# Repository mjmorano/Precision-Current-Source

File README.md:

# Overview
This is all of the design files and the code needed for my precision current source. The code for the microcontroller was made using the Arduino framework and PlatformIO so it's easy to modify and can be uploaded without neededing a programmer, just an Arduino. The serial interface features a few basic commands for setting the current and reading it back using the onboard ADC, as well as reading the internal temperature sensors. I added a lot of error checking to the firmware so it should be basically impossible to make the device do something that it shouldn't, and give the user feedback if their inputs are accepted or not. This design uses an external voltage source up to 100 volts, so it can be used with relatively high resistance loads. It is also suitable for high inductance loads, and has been verified stable into 250 mH. The KiCad folder contains all of the schematics and the .zip files with the gerbers needed to have the PCBs and the front panel manufactured. I have the front panels made as aluminum PCBs with no copper layers, which pretty much any manufacturer can do.

# Stability Measurement
Since this is meant to be used for driving gradient and shim coils for long experimental runs, temperature stability is critical. To measure the stability I rented a Keysight 3458A and logged data for a week at maximum output current and the result can be seen in the plot below. Allan deviations for this data are also shown. The current stability could be further improved by using a different voltage reference, the LTZ1000A or LM399 for example, but these would come with a significant accuracy penalty. Of course the accuracy can be calibrated in software, but that requires the user to have a very good DMM and makes the assembly process more complicated. I tried to balance initial accuracy and temperature stability as much as possible.

# Flashing the Firmware
To upload the program to the microcontroller, the Arduino bootloader needs to be burned. It's possible to buy the microcontroller with the bootloader already installed, but it's easy to do yourself. The best way to do this is in the Arduino IDE, and I'll outline how to do it with either an Uno or a Nano. First the ArduinoISP sketch needs to be uploaded to Arduino and can be found under the example sketches as shown below.

Once it's uploaded connect the Arduino pins to the 6 pin header on the current source as follows:

  | Arduino | Current Source |
  |:-------:|:--------------:|
  |    10   |    RESET       |
  |    11   |    MOSI        |
  |    12   |    MISO        |
  |    13   |    SCK         |
  |    5V   |    5V          |
  |   GND   |    GND         |

Next under tools set the programmer to be "Arduino as ISP", then click burn bootloader. If everything is working right a message should pop up in the bottom right corner of the Arduino IDE saying "Burning bootloader...", followed by a message saying "Done burning bootloader."

Now that the bootloader is burned open the Code/Microcontroller folder from the repo in VS Code, making sure to have the PlatformIO extension installed. After PlatformIO initializes select the port for the Arduino that was used to burn the bootloader in the bottom left, for me it was COM5.
<p align="center">
  <Img src=https://github.com/user-attachments/assets/bcefc186-d4b8-4972-8e65-b901564c9881 />
</p>

After this all that needs to be done is to click the upload button and the terminal should look like the below image.
<p align="center">
  <Img src=https://github.com/user-attachments/assets/629b103b-d0d7-43b1-95bc-183c9badbdb2 />
  <Img src=https://github.com/user-attachments/assets/536357de-a0ee-4a5f-8675-916f626b76a4 />
</p>

Now the device is ready to be connected over USB to a computer.

# Serial Interface
When the device is connected to the computer it should show up as a COM port in windows and a ttyUSB device on Linux. On Linux the device will need to be chmodded in order to connect to it using pyserial. Usually the FTDI drivers automatically download or are already installed, but if not they can be downloaded [here](https://ftdichip.com/drivers/vcp-drivers/). The interface uses eight data bits, no parity, and one stop bit at 115200 baud. On powerup the device does some self checks and looks to see if the optional tmp117 temperature sensor is present. After connecting to the serial interface two readlines need to be done, the first says whether the tmp117 is detected or not, and the second is for any detected errors. If the device detects no errors the second readline will return "Ready." Examples of how to use pyserial with the device are shown in the Code/Serial_Interface_Examples.py file. There are some other commands not shown there, but they won't really be used.

# Schematics
[Precision Current Source.pdf](https://github.com/user-attachments/files/20560946/Precision.Current.Source.pdf)

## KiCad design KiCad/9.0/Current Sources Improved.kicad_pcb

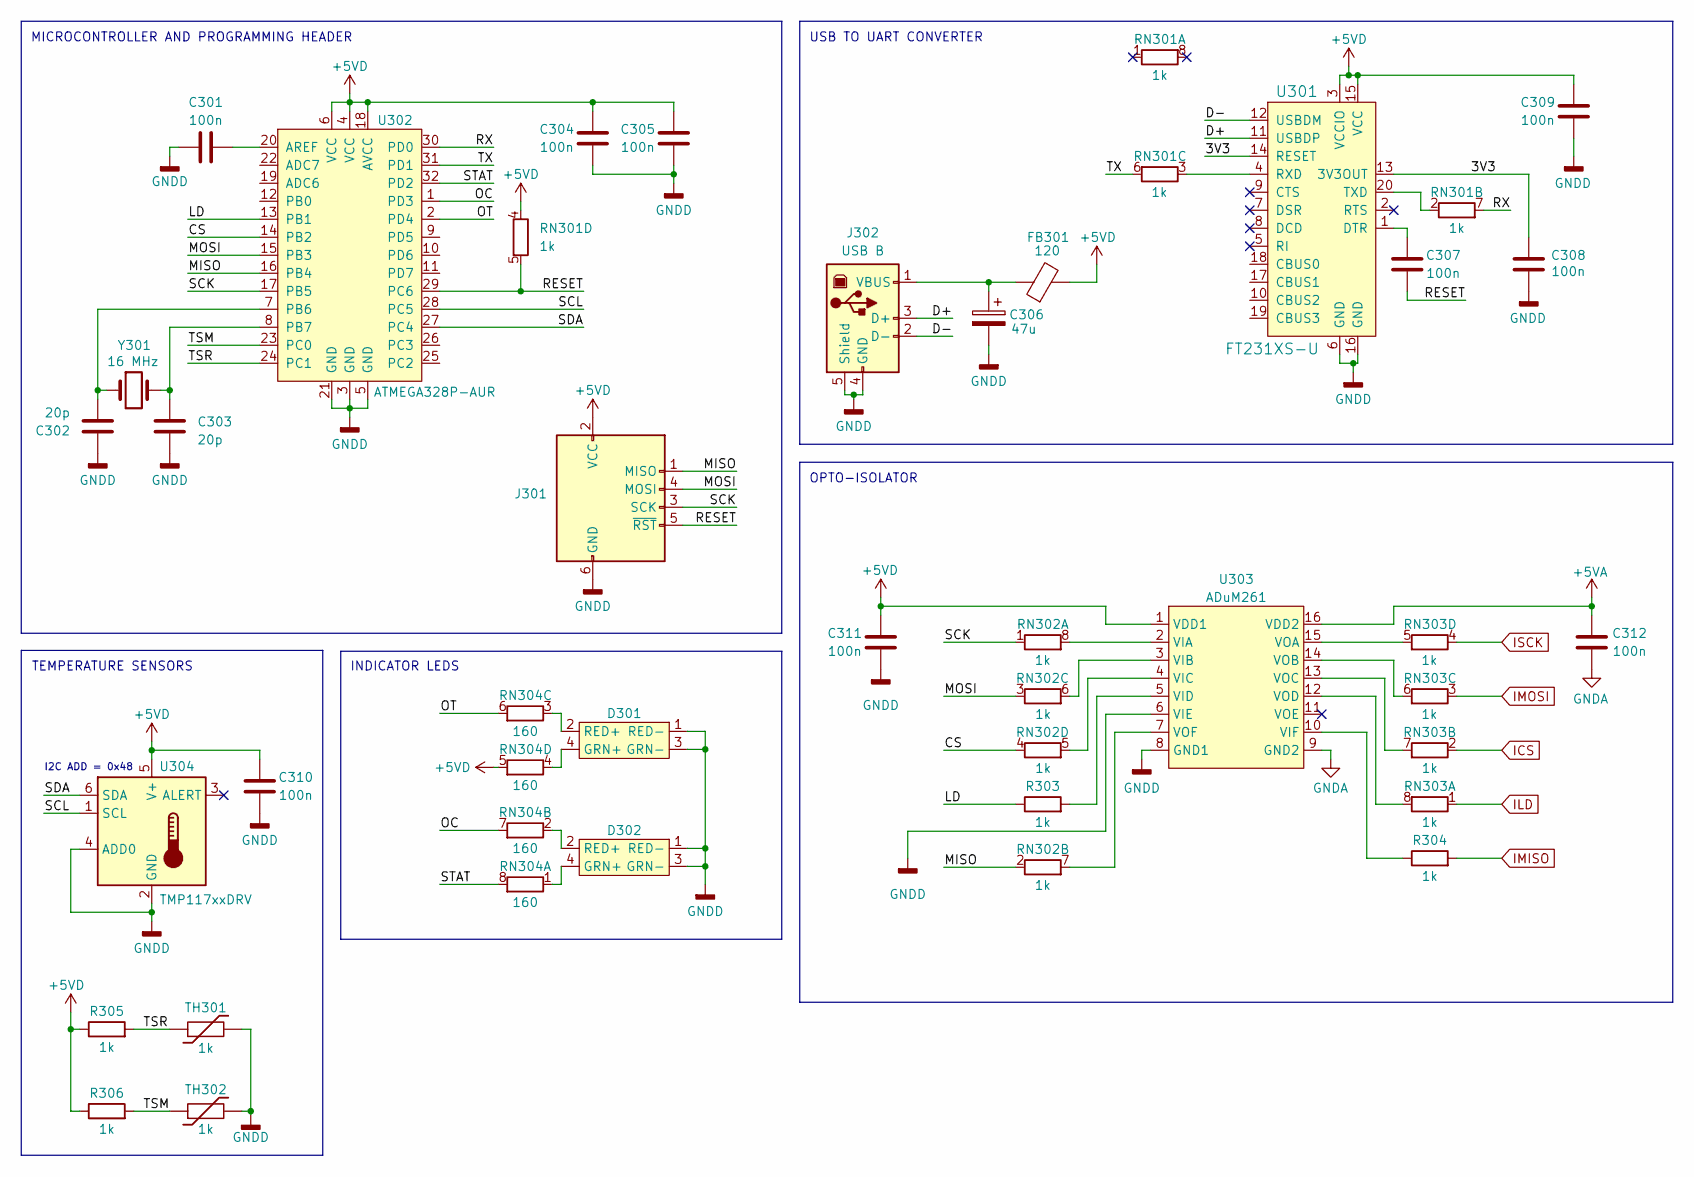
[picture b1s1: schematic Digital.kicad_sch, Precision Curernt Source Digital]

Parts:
C301, C304, C305, C307, C308, C309, C310, C311, C312: 100n; C_0603_1608Metric
C302, C303: 20p; C_0603_1608Metric
C306: 47u; CP_Elec_6.3x5.8
D301, D302: WP934MD
FB301: 120; R_0603_1608Metric
J301: AVR-ISP-6; PinHeader_2x03_P2.54mm_Vertical
J302: USB B; UJ2-BH-1-TH_CUD
R303, R304, R305, R306: 1k; R_0603_1608Metric
RN301, RN302, RN303: 1k; R_Array_Concave_4x0603
RN304: 160; R_Array_Concave_4x0603
TH301, TH302: 1k; PinHeader_1x02_P2.54mm_Vertical
U301: FT231XS-U; SSOP-20_W3.9mm; MPN FT231XS-U; Digi-Key_PN 768-1156-5-ND
U302: ATMEGA328P-AUR; TQFP-32_7x7mm; MPN ATMEGA328P-AUR; Digi-Key_PN ATMEGA328P-AURCT-ND
U303: ADuM261; SOIC-16W_7.5x12.8mm_P1.27mm
U304: TMP117xxDRV; WSON-6-1EP_2x2mm_P0.65mm_EP1x1.6mm
Y301: 16 MHz; XTAL_ECS-200-20-3X-TR

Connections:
+5VA: C312.2, U303.16 (VDD2); also elsewhere on the board
+5VD: C304.1, C305.2, C309.2, C310.1, C311.2, FB301.2, J301.2 (VCC), R305.1, R306.1, RN301.4 (R4.1), RN304.5 (R4.2), U301.3 (VCCIO), U301.15 (VCC), U302.4 (VCC), U302.6 (VCC), U302.18 (AVCC), U303.1 (VDD1), U304.5 (V+); also elsewhere on the board
/Digital/3V3: C308.1, U301.13 (3V3OUT), U301.14 (RESET)
/Digital/CS: RN302.4 (R4.1), U302.14 (PB2)
/Digital/D+: J302.3 (D+), U301.11 (USBDP)
/Digital/D-: J302.2 (D-), U301.12 (USBDM)
/Digital/LD: R303.1, U302.13 (PB1)
/Digital/MISO: J301.1 (MISO), RN302.2 (R2.1), U302.16 (PB4)
/Digital/MOSI: J301.4 (MOSI), RN302.3 (R3.1), U302.15 (PB3)
/Digital/OC: RN304.7 (R2.2), U302.1 (PD3)
/Digital/OT: RN304.6 (R3.2), U302.2 (PD4)
/Digital/RESET: C307.1, J301.5 (~RST), RN301.5 (R4.2), U302.29 (PC6)
/Digital/RX: RN301.7 (R2.2), U302.30 (PD0)
/Digital/SCK: J301.3 (SCK), RN302.1 (R1.1), U302.17 (PB5)
/Digital/SCL: U302.28 (PC5), U304.1 (SCL)
/Digital/SDA: U302.27 (PC4), U304.6 (SDA)
/Digital/STAT: RN304.8 (R1.2), U302.32 (PD2)
/Digital/TSM: R306.2, TH302.1, U302.23 (PC0)
/Digital/TSR: R305.2, TH301.1, U302.24 (PC1)
/Digital/TX: RN301.6 (R3.2), U302.31 (PD1)
GNDA: C312.1, U303.9 (GND2); also elsewhere on the board
GNDD: C301.2, C302.1, C303.2, C304.2, C305.1, C306.2, C308.2, C309.1, C310.2, C311.1, D301.1 (RED-), D301.3 (GRN-), D302.1 (RED-), D302.3 (GRN-), J301.6 (GND), J302.4 (GND), J302.5 (Shield), TH301.2, TH302.2, U301.6 (GND), U301.16 (GND), U302.3 (GND), U302.5 (GND), U302.21 (GND), U303.6 (VIE), U303.8 (GND1), U304.2 (GND), U304.4 (ADD0); also elsewhere on the board
ICS: RN303.2 (R2.1); also elsewhere on the board
ILD: RN303.1 (R1.1); also elsewhere on the board
IMISO: R304.2; also elsewhere on the board
IMOSI: RN303.3 (R3.1); also elsewhere on the board
ISCK: RN303.4 (R4.1); also elsewhere on the board
unnamed: D301.4 (GRN+), RN304.4 (R4.1)
unnamed: D301.2 (RED+), RN304.3 (R3.1)
unnamed: D302.4 (GRN+), RN304.1 (R1.1)
unnamed: D302.2 (RED+), RN304.2 (R2.1)
unnamed: C306.1, FB301.1, J302.1 (VBUS)
unnamed: RN301.2 (R2.1), U301.20 (TXD)
unnamed: RN301.3 (R3.1), U301.4 (RXD)
unnamed: RN302.8 (R1.2), U303.2 (VIA)
unnamed: RN302.7 (R2.2), U303.7 (VOF)
unnamed: RN302.6 (R3.2), U303.3 (VIB)
unnamed: RN302.5 (R4.2), U303.4 (VIC)
unnamed: RN303.8 (R1.2), U303.12 (VOD)
unnamed: RN303.7 (R2.2), U303.13 (VOC)
unnamed: RN303.6 (R3.2), U303.14 (VOB)
unnamed: RN303.5 (R4.2), U303.15 (VOA)
unnamed: C307.2, U301.1 (DTR)
unnamed: C301.1, U302.20 (AREF)
unnamed: C302.2, U302.7 (PB6), Y301.1
unnamed: C303.1, U302.8 (PB7), Y301.2
unnamed: R303.2, U303.5 (VID)
unnamed: R304.1, U303.10 (VIF)

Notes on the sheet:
MICROCONTROLLER AND PROGRAMMING HEADER
TEMPERATURE SENSORS
INDICATOR LEDS
USB TO UART CONVERTER
I2C ADD = 0x48
OPTO-ISOLATOR

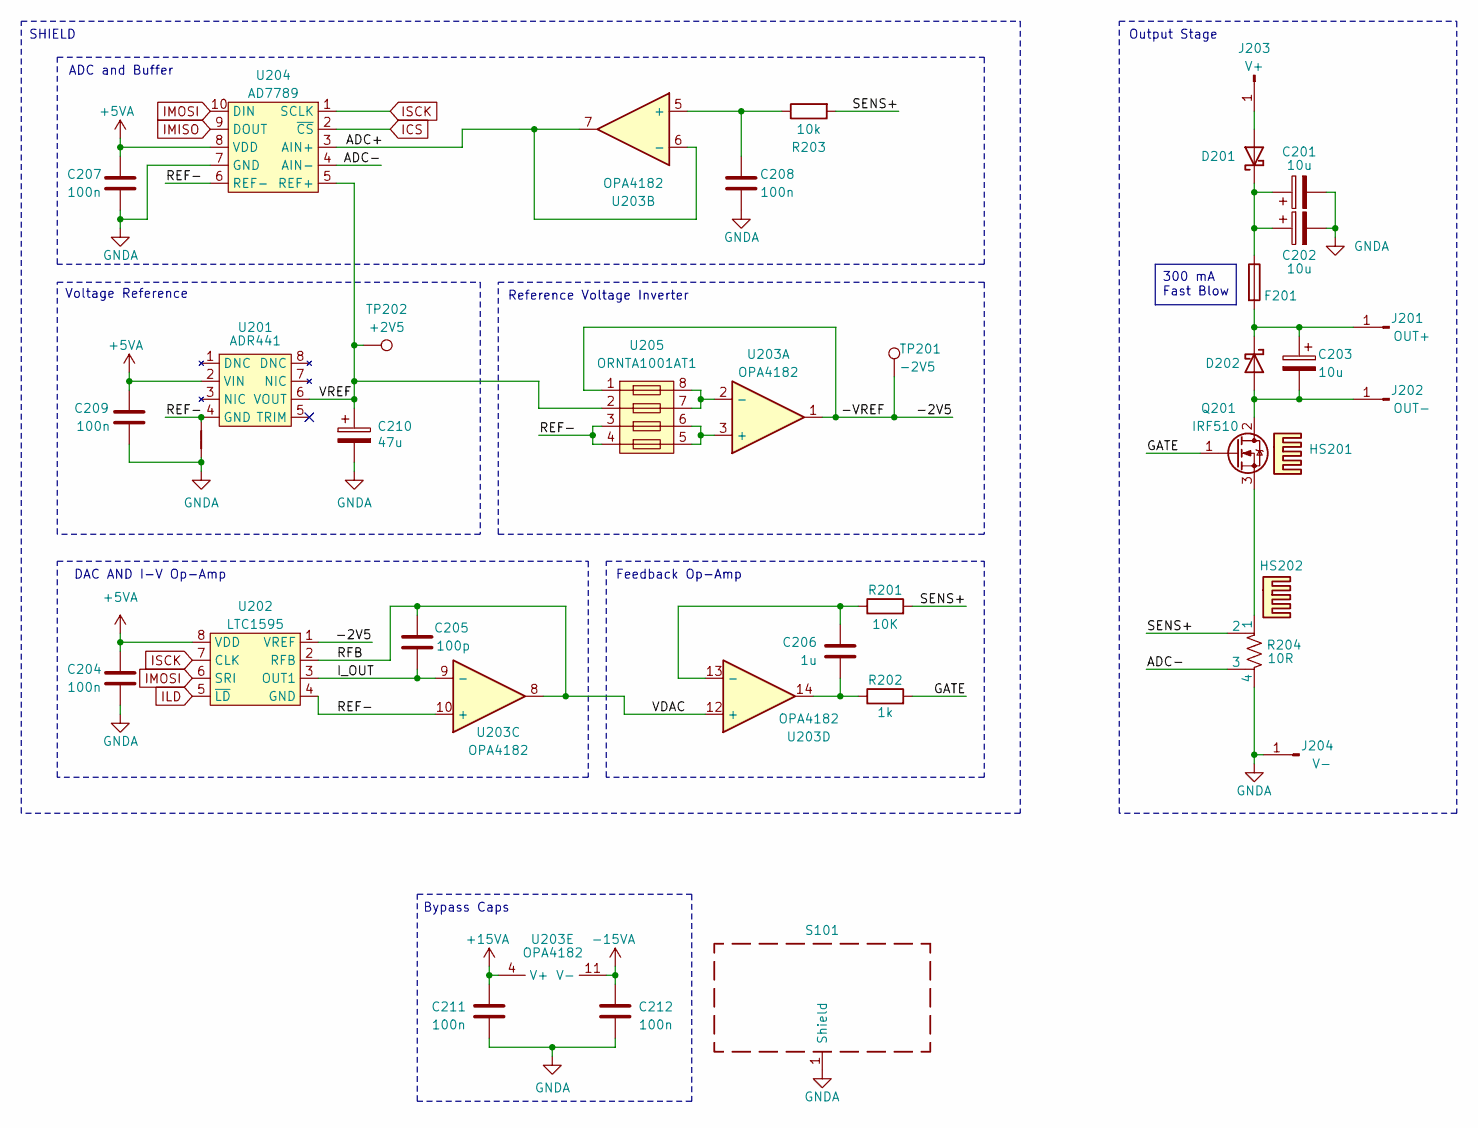
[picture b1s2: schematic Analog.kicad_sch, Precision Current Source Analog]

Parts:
C201, C202, C203: 10u; CP_Elec_6.3x5.8
C204, C207, C208, C209, C211, C212: 100n; C_0603_1608Metric
C205: 100p; C_0603_1608Metric
C206: 1u; CB05_AVX
C210: 47u; CP_Elec_6.3x5.8
D201, D202: D_Schottky; D_SOD-123F
F201: Fuse; 0031.7701.22
HS201: 530002B02500G; 529802B02500G; Mouser Part Number 532-530002B02500G
HS202: Heatsink; 577102B04000G
J201: OUT+; 1211
J202: OUT-; 1211
J203: V+; 1211
J204: V-; 1211
NT201: NetTie_2; SmallNetTie
Q201: IRF510; TO-220-3_Vertical
R201: 10K; R_0603_1608Metric
R202: 1k; R_0603_1608Metric
R203: 10k; R_0603_1608Metric
R204: 10R; TO-220-4_Vertical
S101: RFShield_OnePiece; Laird_Technologies_BMI-S-204-F_32.00x32.00mm
TP201: -2V5; TestPoint_Pad_D1.0mm
TP202: +2V5; TestPoint_Pad_D1.0mm
U201: ADR441; SOIC-8_3.9x4.9mm_P1.27mm
U202: LTC1595; SOIC-8_3.9x4.9mm_P1.27mm
U203: OPA4182; SOIC-14_3.9x8.7mm_P1.27mm
U204: AD7789; MSOP-10_3x3mm_P0.5mm
U205: ORNTA1001AT1; SOIC-8_3.9x4.9mm_P1.27mm

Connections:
+5VA: C204.1, C207.1, C209.1, U201.2 (VIN), U202.8 (VDD), U204.8 (VDD); also elsewhere on the board
+15VA: C211.2, U203.4 (V+); also elsewhere on the board
-15VA: C212.2, U203.11 (V-); also elsewhere on the board
/Analog/-2V5: TP201.1, U202.1 (VREF), U203.1, U205.1
/Analog/ADC+: U203.6 (-), U203.7, U204.3 (AIN+)
/Analog/ADC-: R204.3, U204.4 (AIN-)
/Analog/GATE: Q201.1 (G), R202.2
/Analog/I_OUT: C205.2, U202.3 (OUT1), U203.9 (-)
/Analog/REF-: NT201.2, U201.4 (GND), U202.4 (GND), U203.10 (+), U204.6 (REF-), U205.3, U205.4
/Analog/RFB: C205.1, U202.2 (RFB), U203.8, U203.12 (+)
/Analog/SENS+: R201.2, R203.2, R204.2
/Analog/VREF: C210.1, TP202.1, U201.6 (VOUT), U204.5 (REF+), U205.2
GNDA: C201.2, C202.2, C204.2, C207.2, C208.2, C209.2, C210.2, C211.1, C212.1, J204.1, NT201.1, R204.4, S101.1 (Shield), U204.7 (GND); also elsewhere on the board
ICS: U204.2 (~CS); also elsewhere on the board
ILD: U202.5 (~LD); also elsewhere on the board
IMISO: U204.9 (DOUT); also elsewhere on the board
IMOSI: U202.6 (SRI), U204.10 (DIN); also elsewhere on the board
ISCK: U202.7 (CLK), U204.1 (SCLK); also elsewhere on the board
unnamed 40: C206.2, R202.1, U203.14; also elsewhere on the board
unnamed: D201.2 (A), J203.1
unnamed: C201.1, C202.1, D201.1 (K), F201.1
unnamed: C203.2, D202.2 (A), J202.1, Q201.2 (D)
unnamed: C203.1, D202.1 (K), F201.2, J201.1
unnamed: Q201.3 (S), R204.1
unnamed: U203.3 (+), U205.5, U205.6
unnamed: U203.2 (-), U205.7, U205.8
unnamed: C208.1, R203.1, U203.5 (+)
unnamed 68: C206.1, R201.1, U203.13 (-); also elsewhere on the board

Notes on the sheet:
ADC and Buffer
SHIELD
Reference Voltage Inverter
Feedback Op-Amp
Voltage Reference
DAC AND I-V Op-Amp
Output Stage
Bypass Caps
300 mA Fast Blow

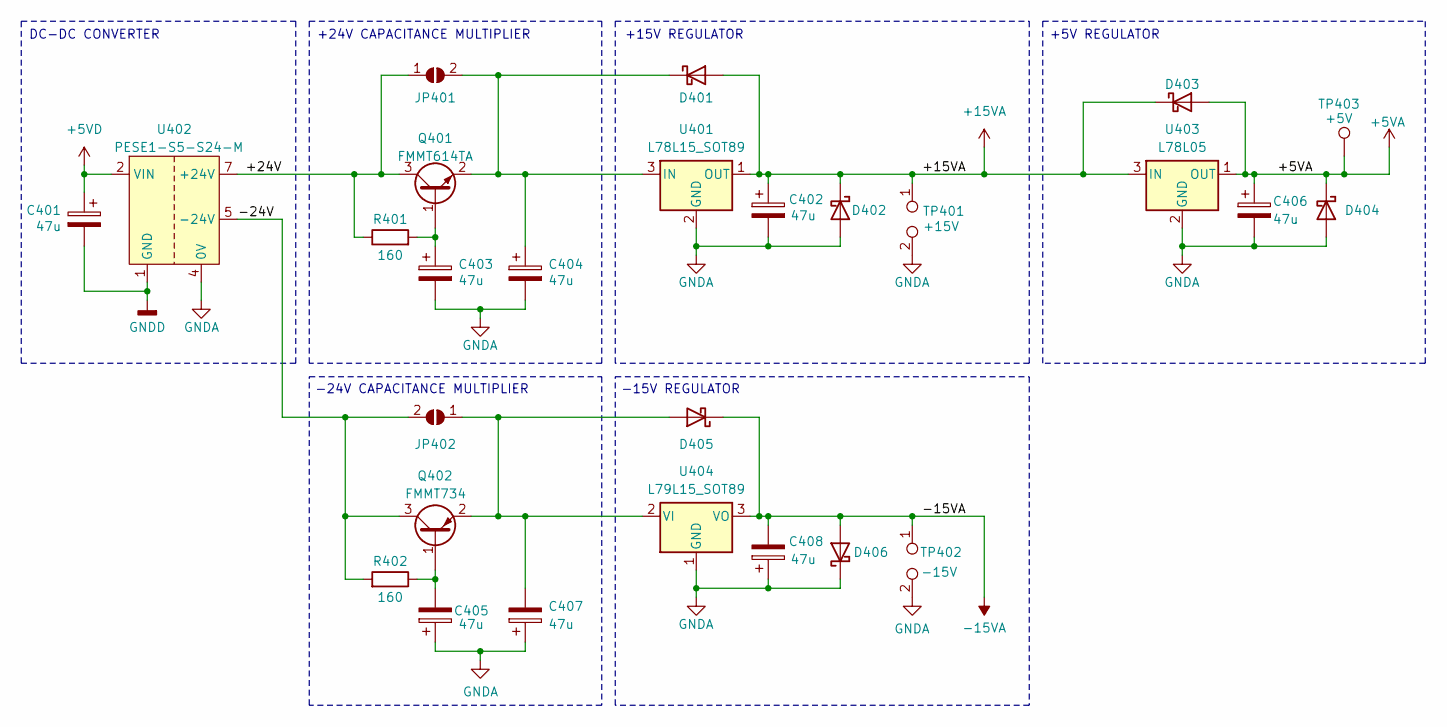
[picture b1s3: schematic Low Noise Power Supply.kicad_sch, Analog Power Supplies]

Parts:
C401, C402, C403, C404, C405, C406, C407, C408: 47u; CP_Elec_6.3x5.8
D401, D402, D403, D404, D405, D406: D_Schottky; D_SOD-123F
JP401, JP402: SolderJumper_2_Open; SolderJumper-2_P1.3mm_Open_RoundedPad1.0x1.5mm
Q401: FMMT614TA; SOT-23-3
Q402: FMMT734; SOT-23-3
R401, R402: 160; R_0603_1608Metric
TP401: +15V; testPoint2Pads
TP402: -15V; testPoint2Pads
TP403: +5V; TestPoint_Pad_D1.0mm
U401: L78L15_SOT89; SOT-89-3
U402: PESE1-S5-S24-M; PDS1-S5-D15-M-TR
U403: L78L05; SOT-89-3
U404: L79L15_SOT89; SOT-89-3

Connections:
+5VA: C406.1, D403.2 (A), D404.1 (K), TP403.1, U403.1 (OUT); also elsewhere on the board
+5VD: C401.1, U402.2 (VIN); also elsewhere on the board
+15VA: C402.1, D401.2 (A), D402.1 (K), D403.1 (K), TP401.1, U401.1 (OUT), U403.3 (IN); also elsewhere on the board
-15VA: C408.2, D405.1 (K), D406.2 (A), TP402.1, U404.3 (VO); also elsewhere on the board
/POWER/+24V: JP401.1 (A), Q401.3 (C), R401.1, U402.7 (+24V)
/POWER/-24V: JP402.2 (B), Q402.3 (C), R402.2, U402.5 (-24V)
GNDA: C402.2, C403.2, C404.2, C405.1, C406.2, C407.1, C408.1, D402.2 (A), D404.2 (A), D406.1 (K), TP401.2, TP402.2, U401.2 (GND), U402.4 (0V), U403.2 (GND), U404.1 (GND); also elsewhere on the board
GNDD: C401.2, U402.1 (GND); also elsewhere on the board
unnamed: C404.1, D401.1 (K), JP401.2 (B), Q401.2 (E), U401.3 (IN)
unnamed: C407.2, D405.2 (A), JP402.1 (A), Q402.2 (E), U404.2 (VI)
unnamed: C403.1, Q401.1 (B), R401.2
unnamed: C405.2, Q402.1 (B), R402.1

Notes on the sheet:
-24V CAPACITANCE MULTIPLIER
+24V CAPACITANCE MULTIPLIER
+5V REGULATOR
-15V REGULATOR
DC-DC CONVERTER
+15V REGULATOR

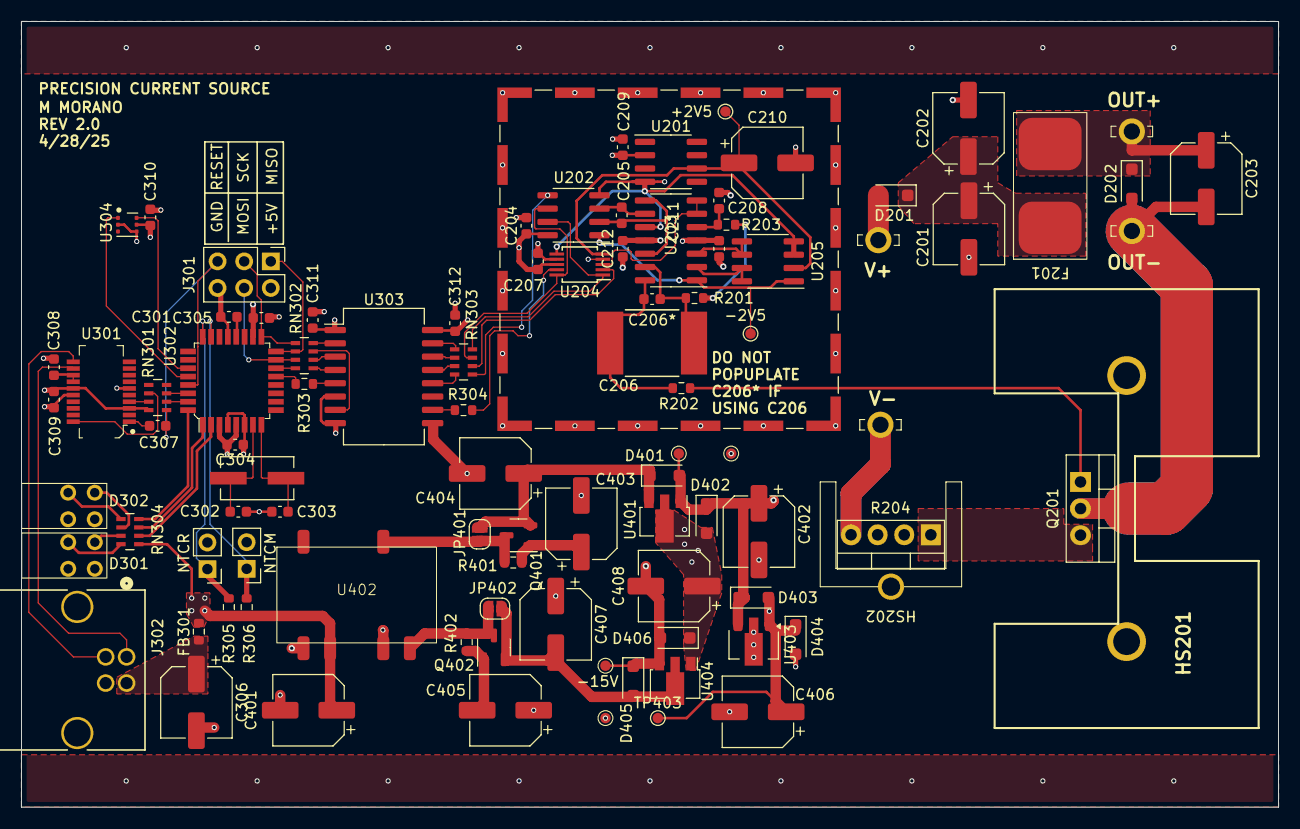
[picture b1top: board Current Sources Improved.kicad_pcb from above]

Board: 4 copper layers, 120.0 x 75.0 mm, 95 parts (1 on the bottom side), 75 nets.

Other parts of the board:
C206*: C_0603_1608Metric

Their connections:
unnamed 40: C206*.1; also elsewhere on the board
unnamed 68: C206*.2; also elsewhere on the board

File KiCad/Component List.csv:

Item,Qty,Reference(s),Value,Footprint,Digikey Part #,Manufacturer part #
1,3,"C201, C204, C213",10u 100V,SMD 6.3x7.7,732-865060845002CT-ND,865060845002
2,15,"C202, C208, C209, C210, C211, C212, C302, C305, C306, C309, C310, C311, C312, C313, C314",100n 50V X7R,0603,399-C0603C104K5RACTUCT-ND,C0603C104K5RACTU
3,10,"C203, C301, C401, C402, C403, C404, C405, C406, C407, C408",47u 35V,SMD 6.3x5.5,732-8508-1-ND,865080543009
4,2,"C205, C207",100p 50V C0G,0603,490-1427-1-ND,GRM1885C1H101JA01D
5,1,C206,1u 100V Film,2824,478-4539-1-ND,CB052E0105JBC
6,2,"C307, C308",20p 50V C0G,0603,1276-1187-1-ND,CL10C200JB8NNNC
7,8,"D201, D202, D401, D402, D403, D404, D405, D406",Schottky 40V,SOD-123F,B140S1F-7,31-B140S1F-7CT-ND
8,2,"D301, D302",Dual LED,WP934MD,754-2010-ND,WP934MD/LILGD
9,1,F201,Fuse Holder,0031.7701.22,486-3856-1-ND,0031.7701.22
10,1,FB301,120,0603,490-5254-1-ND,BLM18KG121TN1D
11,1,HS201,6396BG,6396BG,6396BG-ND,6396BG
12,1,HS202,Heatsink,577102B04000G,HS368-ND,577102B04000G
13,1,"J201, J202, J203, J204",Tab Connector,Through Hole,36-1211-ND,1211
14,1,J301,6 Pin Header,2x3 2.54 Through Hole,952-2121-ND,M20-9980346
15,1,J302,USB B,Through Hole Right Angle,102-3999-ND,UJ2-BH-1-TH
16,1,Q201,IRF510,TO-220-3,IRF510PBF-ND,IRF510PBF
17,1,Q401,FMMT614TA,SOT-23-3,FMMT614CT-ND,FMMT614TA
18,1,Q402,FMMT734,SOT-23-3,FMMT734CT-ND,FMMT734TA
19,1,R201,10K,0603,RMCF0603JT10K0CT-ND,RMCF0603JT10K0
20,6,"R202, R203, R303, R304, R305, R306",1k,0603,RMCF0603FT1K00CT-ND,RMCF0603FT1K00
21,1,R204,10R,TO-220-4,Y0926-10A-ND,Y092610R0000T9L
22,2,"R401, R402",160,0603,311-160GRCT-ND,RC0603JR-07160RL
23,3,"RN301, RN302, RN303",1k,4x0603,60-742C083102JPCT-ND,742C083102JP
24,1,RN304,120,4x0603,Y4121CT-ND,EXB-V8V121JV
25,1,S101,RF Shield Frame,32x32,903-BMI-S-204-FCT-ND,BMI-S-204-F
26,2,"TH301, TH302",1k NTC,Through Hole,900-2152723107-ND,2152723107
27,1,U201,ADR441B,SOIC-8,505-ADR441BRZ-ND,ADR441BRZ
28,1,U202,LTC1595B,SOIC-8,LTC1595BCS8#TRPBFCT-ND,LTC1595BCS8#TRPBF
29,1,U203,OPA4182,SOIC-14,296-OPA4182IDRCT-ND,OPA4182IDR
30,1,U204,AD7789,MSOP-10,AD7789BRMZ-REELCT-ND,AD7789BRMZ-REEL
31,1,U205,1k,SOIC-8,ORNT-1KACT-ND,ORNTA1001AT1
32,1,U301,FT231XS-U,SSOP-10,768-1156-5-ND,FT231XS-U
33,1,U302,ATMEGA328P,TQFP-32,ATMEGA328P-AU-ND,ATMEGA328P-AU
34,1,U303,ADuM261N0,SOIC-16 7.5W,505-ADUM261N0BRIZ-ND,ADUM261N0BRIZ
35,1,U304,TMP117xxDRV,WSON-6,296-51835-1-ND,TMP117MAIDRVR
36,1,U401,L78L15,SOT-89-3,497-7769-1-ND,L78L15ABUTR
37,1,U402,PESE1-S5-S24-M,SMD-10 Module,PESE1-S5-D24-M-TR,PESE1-S5-D24-M-TR
38,1,U403,L78L05,SOT-89-3,497-1181-1-ND,L78L05ABUTR
39,1,U404,L79L15,SOT-89-3,497-L79L15ACUCT-ND,L79L15ACUTR
40,1,Y301,16 MHz,HC-49/US,XC1776CT-ND,ECS-160-20-3X-TR
,,,,,,
Mechanical Parts,,,,,,
Item,Qty,Description,Digikey Part #,Manufacturer Part #,,
1,1,RF Shield Cover,903-1016-ND,BMI-S-204-C,,
2,1,Terminal Block Header,277-5988-ND,707264,,
3,1,Terminal Block,277-1013-ND,1757035,,
4,2,Terminal Block Mounting Screw,277-5786-ND,0708263,,
5,1,Enclosure,HM972-ND,1455K1201,,
6,8,Crimp Connector,277-17467-ND,3240535,,
7,8,"6-32x3/8"" Screw",PMS 632 0038 PH,H356-ND,,
8,1,350 mA Fast Blow Fuse,486-3000-ND,3404.0043.11,,

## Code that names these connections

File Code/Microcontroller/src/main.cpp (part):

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#include "AD7789.h"

// Do all the setup stuff
#define STAT 2      // Stats LED pin
#define OC 3        // Overcurrent LED pin
#define OT 4        // Overtemp LED pin
#define LD 9        // LD pin for the LTC1595
#define TSR A0      // Resistor NTC on ADC channel 0
#define TSM A1      // MOSFET NTC on ADC channel 1

const float maxAdcCode = pow(2, 24);        // Max code for 24 bit ADC
const float maxDacCode = pow(2, 16) - 1;    // Max code for 16 bit DAC
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  digitalWrite(OT, LOW);
  pinMode(OC, OUTPUT);
  digitalWrite(OC, LOW);
  pinMode(STAT, OUTPUT);
  digitalWrite(STAT, LOW);       
  digitalWrite(SS, HIGH);		  
  pinMode(LD, OUTPUT);                
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
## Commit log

2025-04-23 added reamde
2025-04-25 Removed debug stuff
2025-04-28 Added pyserial example and cleaned up some stuff
2025-04-28 Removed port
2025-04-28 Adjusted designators for NTCs
2025-04-28 Fixed the ADC scaling
2025-04-28 Made a few changes
2025-04-29 Updated some designators and added component list
2025-04-29 Changed part list to .xlsx so formatting would save
2025-05-01 Cleaned up a few things
2025-05-01 Added ibom overlay
2025-06-03 Updated KiCad project to version 9
